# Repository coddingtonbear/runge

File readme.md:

# Runge: Convert a Sboly Coffee Grinder into a Doser

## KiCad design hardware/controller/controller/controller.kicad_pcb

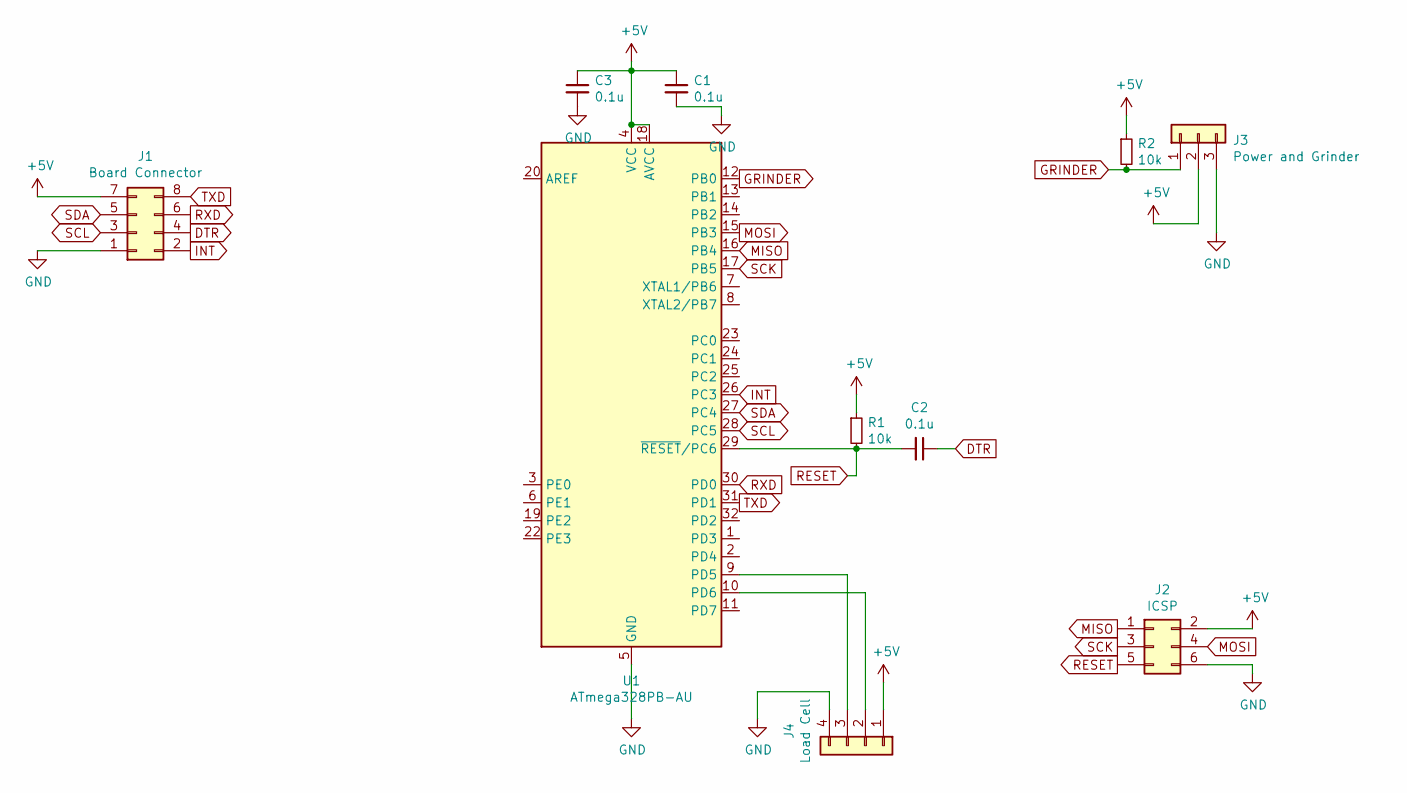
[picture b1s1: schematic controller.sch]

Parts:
C1, C2, C3: 0.1u; 0805_Milling
J1: Board Connector; IDC-Header_2x04_P2.54mm_Vertical
J2: ICSP; PinHeader_2x03_P2.54mm_Vertical
J3: Power and Grinder; PinHeader_1x03_P2.54mm_Vertical
J4: Load Cell; PinHeader_1x04_P2.54mm_Vertical
R1, R2: 10k; 0805_Milling
U1: ATmega328PB-AU; TQFP-32_7x7mm_P0.8mm

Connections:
+5V: C1.1, C3.1, J1.7, J2.2, J3.2, J4.1, R1.1, R2.1, U1.4 (VCC), U1.18 (AVCC)
DTR: C2.1, J1.4
GND: C1.2, C3.2, J1.1, J2.6, J3.3, J4.4, U1.5 (GND), U1.21 (GND)
GRINDER: J3.1, R2.2, U1.12 (PB0)
INT: J1.2, U1.26 (PC3)
MISO: J2.1, U1.16 (PB4)
MOSI: J2.4, U1.15 (PB3)
unnamed: J4.2, U1.10 (PD6)
unnamed: J4.3, U1.9 (PD5)
RESET: C2.2, J2.5, R1.2, U1.29 (~RESET~/PC6)
RXD: J1.6, U1.30 (PD0)
SCK: J2.3, U1.17 (PB5)
SCL: J1.3, U1.28 (PC5)
SDA: J1.5, U1.27 (PC4)
TXD: J1.8, U1.31 (PD1)

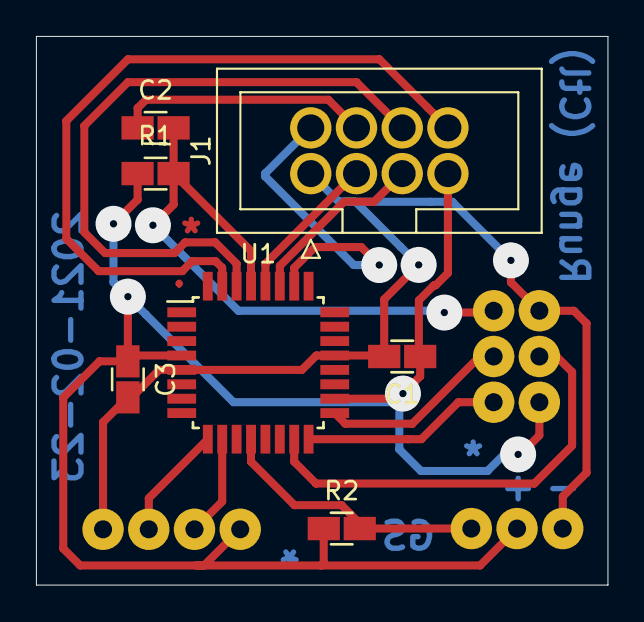
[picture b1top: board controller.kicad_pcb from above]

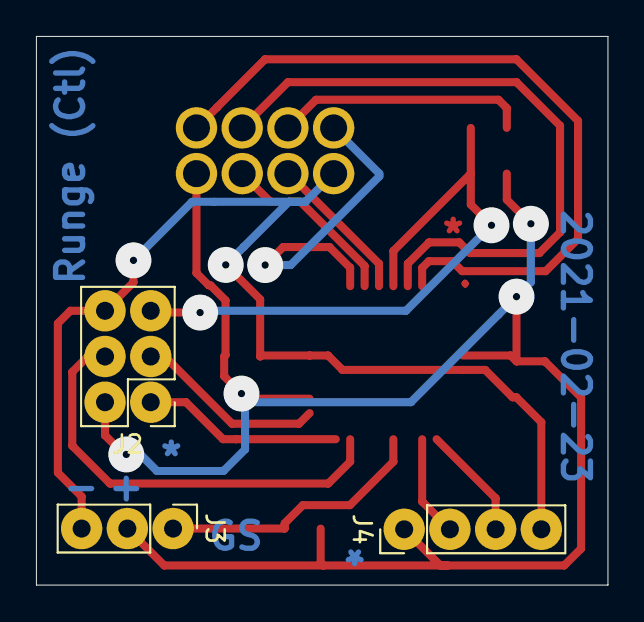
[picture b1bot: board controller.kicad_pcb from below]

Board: 2 copper layers, 31.8 x 30.5 mm, 10 parts (3 on the bottom side), 15 nets.

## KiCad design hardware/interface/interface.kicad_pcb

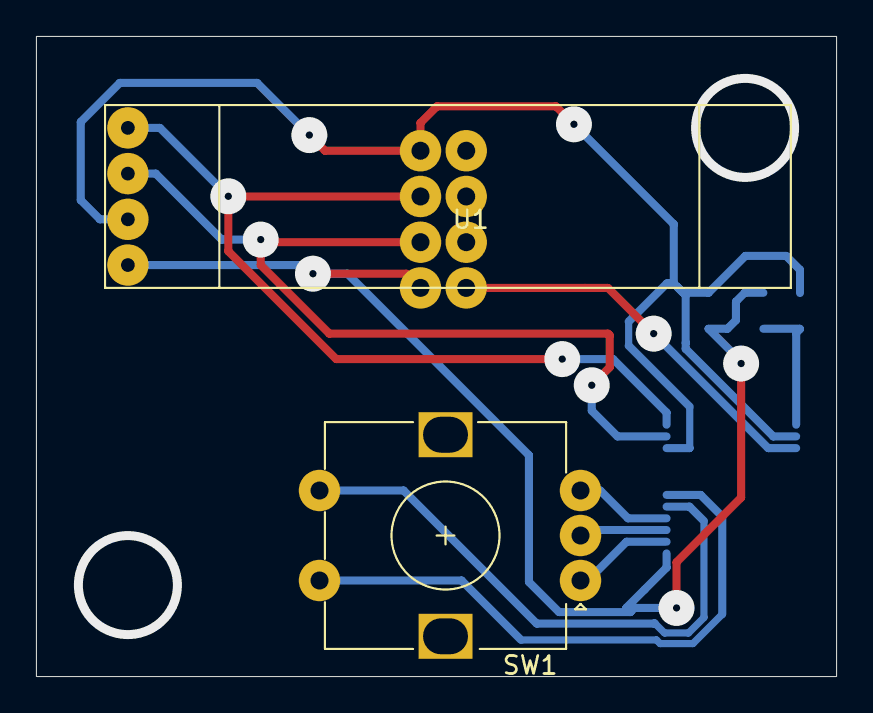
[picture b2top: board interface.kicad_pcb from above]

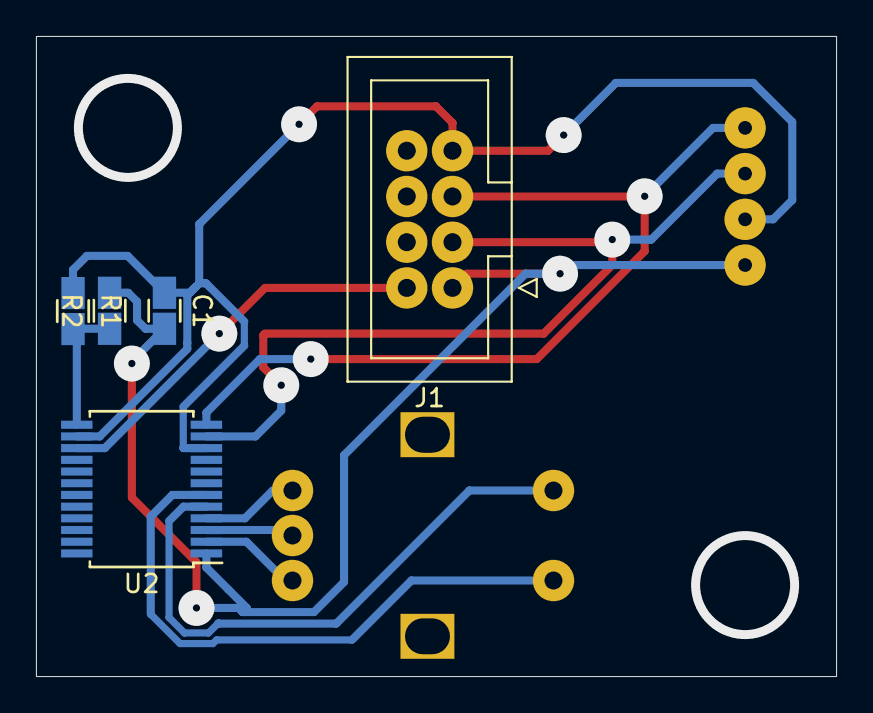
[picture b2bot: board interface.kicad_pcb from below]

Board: 2 copper layers, 44.4 x 35.6 mm, 7 parts (5 on the bottom side), 11 nets.

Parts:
C1: 0.1u; 0805_Milling
J1: Board Connector; IDC-Header_2x04_P2.54mm_Vertical
R1: 15k; 0805_Milling
R2: 1k; 0805_Milling
SW1: Rotary_Encoder_Switch; RotaryEncoder_Alps_EC12E-Switch_Vertical_H20mm
U1: 128x32_OLED
U2: MCP23018-E_SS; SSOP-24_5.3x8.2mm_P0.65mm

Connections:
+5V: C1.1, J1.7, R1.1, U1.2, U2.10, U2.14
GND: C1.2, J1.1, R2.2, U1.1, U2.1
INT: J1.2, U2.15
unnamed: R1.2, R2.1, U2.13
unnamed: SW1.A, U2.2
unnamed: SW1.B, U2.4
unnamed: SW1.C, U2.3
unnamed: SW1.S1, U2.6
unnamed: SW1.S2, U2.5
SCL: J1.3, U1.3, U2.11
SDA: J1.5, U1.4, U2.12

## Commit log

2021-02-14 And so it begins.
2021-02-14 Separate projects per-board.
2021-02-14 Fixing via sizes.
2021-02-14 Fixing mounting hole sizes.
2021-02-15 Whoops; the connector should be on the back side of the board.
2021-02-16 Adding firmware prototype.
2021-02-16 Handle the various state changes necessary.
2021-02-16 Fixing button behavior.
2021-02-16 Enable WDT; emit messages over serial bus for troubleshooting.
2021-02-16 Just...poll the buttons; the interrupt-based method was a little too buggy.
2021-02-16 Render to screen only if message has changed.
2021-02-16 Allow unlikely numbers of grams of coffee.
2021-02-16 Do not display a calibration completed message.
2021-02-17 Adding new controller board.
2021-02-17 Adding connector for load cell amplifier board.
2021-02-24 Updating interface PCB.
2021-02-24 Updating runge controller for new milling process.
2021-03-21 Final weight-based method for dosing.
2021-03-22 Switching to time-based dosing (for the moment).
    When doing initial experiments with the assembled project, the weight
    measurements were found to be going a little crazy the moment the motor
    turned on. I'm not at the moment sure whether the problem is EMI from
    the motor, or if it's just vibration. In any case, the load cell method
    is non-viable for the moment, and I need my coffee grinder. So:
    time-based measurements it is for now.
2021-05-22 Automatically reset after we've made it through half of the ticks that can fit into an unsigned long.
2021-05-22 Automatically reset wdt at start.
2021-05-22 Start countdown from target value instead of one below it.
2021-05-22 Prevent underflow of ulong due to time progressing throughout the loop.
2021-05-22 Handle disconnection from controller board.
2021-05-22 Adds a lockout state for certain error cases.
    - If the grinder has been running for longer than 30s; something
    has gone terribly awry. Shows "ERR: GndT" in such a case.
    - If the interface can't be reached for some reason; we can't
    read button state. Shows "ERR: IfcP" in such a case.
2021-05-22 Do not verify firmware after write.
2021-05-22 Display project/version on-boot.
2021-05-22 Correct reset-after-timeout counter.
2021-05-22 Allow maximally 20s of grinding.
2021-05-22 Swapping fonts to match startup font.
2021-05-22 Display interface state.
